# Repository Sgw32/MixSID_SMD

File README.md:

# MixSID - SMD version
*flexible Stereo-SID-board with integrated channel mixer*

The MixSID is a stereo SID board for the C64 that can be used with any combination 
of SID models on a wide range of C64 mainboards.

Features include an integrated stereo channel mixer, 
pragmatic stereo addressing scheme, flexible handling of io areas,
onboard audio input, output and digiboost circuits, 
dedicated stereo output, full paddle compatibility and versatile digital control.

For more information, please see the project page, available in both 
[english](http://www.henning-bekel.de/mixsid) and [german](http://www.henning-bekel.de/mixsid/de).

SMD version is fully compatible with original one from Henning Bekel, also it is licensed and released as a derivative using GPL license. 

GNU GENERAL PUBLIC LICENSE
Version 2, June 1991 (see more on project page)

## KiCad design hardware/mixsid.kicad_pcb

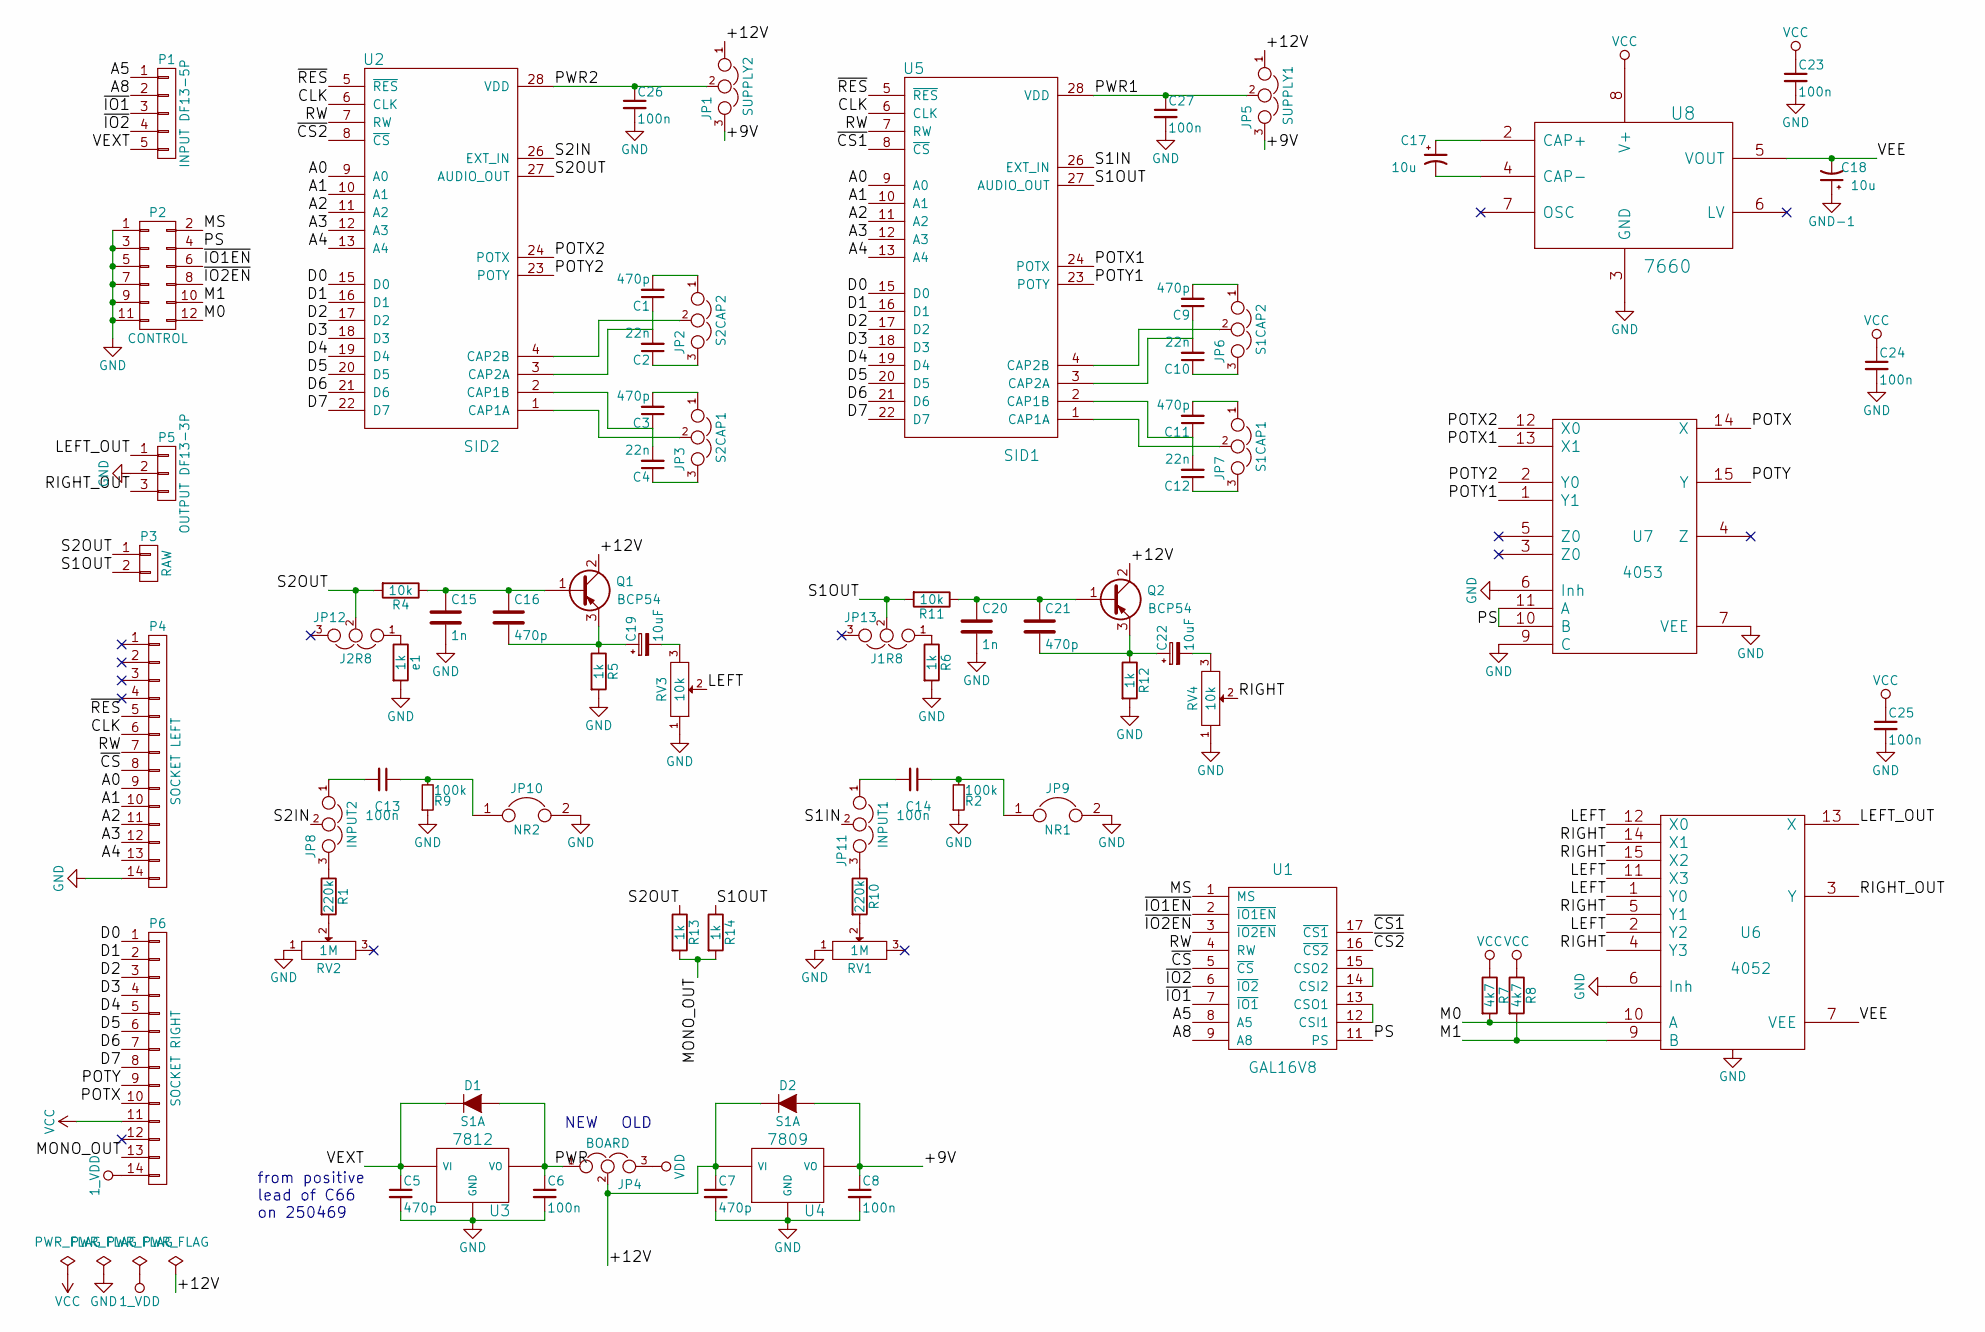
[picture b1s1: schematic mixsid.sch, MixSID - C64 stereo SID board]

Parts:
C1, C3, C5, C7, C9, C11, C16, C21: 470p; 0805
C2, C4, C10, C12: 22n; 0805
C6, C8, C13, C14, C23, C24, C25, C26, C27: 100n; 0805
C15, C20: 1n; 0805
C17, C18: 10u; 0805
C19, C22: 10uF; 0805
D1, D2: S1A; DO-214AC
JP1: SUPPLY2; Pin_Header_Straight_1x03_Pitch2.00mm
JP2: S2CAP2; Pin_Header_Straight_1x03_Pitch2.00mm
JP3: S2CAP1; Pin_Header_Straight_1x03_Pitch2.00mm
JP4: BOARD; Pin_Header_Straight_1x03
JP5: SUPPLY1; Pin_Header_Straight_1x03_Pitch2.00mm
JP6: S1CAP2; Pin_Header_Straight_1x03_Pitch2.00mm
JP7: S1CAP1; Pin_Header_Straight_1x03_Pitch2.00mm
JP8: INPUT2; Pin_Header_Straight_1x03_Pitch2.00mm
JP9: NR1; Pin_Header_Straight_1x02
JP10: NR2; Pin_Header_Straight_1x02
JP11: INPUT1; Pin_Header_Straight_1x03_Pitch2.00mm
JP12: J2R8; Pin_Header_Straight_1x03_Pitch2.00mm
JP13: J1R8; Pin_Header_Straight_1x03_Pitch2.00mm
P1: INPUT DF13-5P; DF13-5P
P2: CONTROL; Pin_Header_Straight_2x06
P3: RAW; Pin_Header_Straight_1x02
P4: SOCKET LEFT; Pin_Header_Straight_1x14
P5: OUTPUT DF13-3P; DF13-3P
P6: SOCKET RIGHT; Pin_Header_Straight_1x14
Q1, Q2: BCP54; SOT-223
R1, R10: 220k; 0805
R2, R9: 100k; 0805
R4, R11: 10k; 0805
R5, R6, R12, R13, R14: 1k; 0805
R7, R8: 4k7; 0805
RV1, RV2: 1M; Potentiometer_Bourns_3296W_3-8Zoll_Inline_ScrewUp
RV3, RV4: 10k; Potentiometer_Bourns_3339P_Angular_ScrewUp
U1: GAL16V8; DIP-20_W7.62mm
U2: SID2; DIP-28_W15.24mm
U3: 7812; TO-252-2
U4: 7809; TO-252-2
U5: SID1; DIP-28_W15.24mm
U6: 4052; SOIC-16
U7: 4053; SOIC-16
U8: 7660; SOIC-8
e1: 1k; 0805

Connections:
/+9V: C8.1, D2.2 (A), JP1.3, JP5.3, U4.3 (VO)
/+12V: C7.1, D2.1 (K), JP1.1, JP4.2, JP5.1, Q1.2 (C), Q2.2 (C), U4.1 (VI)
/A0: P4.9, U2.9 (A0), U5.9 (A0)
/A1: P4.10, U2.10 (A1), U5.10 (A1)
/A2: P4.11, U2.11 (A2), U5.11 (A2)
/A3: P4.12, U2.12 (A3), U5.12 (A3)
/A4: P4.13, U2.13 (A4), U5.13 (A4)
/A5: P1.1, U1.8 (A5)
/A8: P1.2, U1.9 (A8)
/CLK: P4.6, U2.6 (CLK), U5.6 (CLK)
/D0: P6.1, U2.15 (D0), U5.15 (D0)
/D1: P6.2, U2.16 (D1), U5.16 (D1)
/D2: P6.3, U2.17 (D2), U5.17 (D2)
/D3: P6.4, U2.18 (D3), U5.18 (D3)
/D4: P6.5, U2.19 (D4), U5.19 (D4)
/D5: P6.6, U2.20 (D5), U5.20 (D5)
/D6: P6.7, U2.21 (D6), U5.21 (D6)
/D7: P6.8, U2.22 (D7), U5.22 (D7)
/LEFT: RV3.2, U6.1 (Y0), U6.2 (Y2), U6.11 (X3), U6.12 (X0)
/LEFT_OUT: P5.1, U6.13 (X)
/M0: P2.12, R7.2, U6.10 (A)
/M1: P2.10, R8.2, U6.9 (B)
/MONO_OUT: P6.13, R13.2, R14.2
/MS: P2.2, U1.1 (MS)
/POTX: P6.10, U7.14 (X)
/POTX1: U5.24 (POTX), U7.13 (X1)
/POTX2: U2.24 (POTX), U7.12 (X0)
/POTY: P6.9, U7.15 (Y)
/POTY1: U5.23 (POTY), U7.1 (Y1)
/POTY2: U2.23 (POTY), U7.2 (Y0)
/PS: P2.4, U1.11 (PS), U7.10 (B), U7.11 (A)
/PWR: C6.1, D1.2 (A), JP4.1, U3.3 (VO)
/PWR1: C27.1, JP5.2, U5.28 (VDD)
/PWR2: C26.1, JP1.2, U2.28 (VDD)
/RIGHT: RV4.2, U6.4 (Y3), U6.5 (Y1), U6.14 (X1), U6.15 (X2)
/RIGHT_OUT: P5.3, U6.3 (Y)
/RW: P4.7, U1.4 (RW), U2.7 (RW), U5.7 (RW)
/S1IN: JP11.2, U5.26 (EXT_IN)
/S1OUT: JP13.2, P3.2, R11.2, R14.1, U5.27 (AUDIO_OUT)
/S2IN: JP8.2, U2.26 (EXT_IN)
/S2OUT: JP12.2, P3.1, R4.2, R13.1, U2.27 (AUDIO_OUT)
/VEE: C18.2, U6.7 (VEE), U8.5 (VOUT)
/VEXT: C5.1, D1.1 (K), P1.5, U3.1 (VI)
/~CS1: U1.17 (~CS1), U5.8 (~CS)
/~CS2: U1.16 (~CS2), U2.8 (~CS)
/~CS: P4.8, U1.5 (~CS)
/~IO1EN: P2.6, U1.2 (~IO1EN)
/~IO1: P1.3, U1.7 (~IO1)
/~IO2EN: P2.8, U1.3 (~IO2EN)
/~IO2: P1.4, U1.6 (~IO2)
/~RES: P4.5, U2.5 (~RES), U5.5 (~RES)
unnamed: C1.1, C2.2, U2.3 (CAP2A)
unnamed: C1.2, JP2.1
unnamed: C2.1, JP2.3
unnamed: C3.1, C4.2, U2.2 (CAP1B)
unnamed: C3.2, JP3.1
unnamed: C4.1, JP3.3
unnamed: C9.2, JP6.1
unnamed: C10.1, JP6.3
unnamed: C9.1, C10.2, U5.3 (CAP2A)
unnamed: C11.1, C12.2, U5.2 (CAP1B)
unnamed: C11.2, JP7.1
unnamed: C12.1, JP7.3
unnamed: C13.1, JP10.1, R9.2
unnamed: C13.2, JP8.1
unnamed: C14.1, JP9.1, R2.2
unnamed: C14.2, JP11.1
unnamed: C15.1, C16.1, Q1.1 (B), R4.1
unnamed: C16.2, C19.1, Q1.3 (E), R5.1
unnamed: C17.1, U8.2 (CAP+)
unnamed: C17.2, U8.4 (CAP-)
unnamed: C19.2, RV3.3
unnamed: C20.1, C21.1, Q2.1 (B), R11.1
unnamed: C21.2, C22.1, Q2.3 (E), R12.1
unnamed: C22.2, RV4.3
unnamed: JP2.2, U2.4 (CAP2B)
unnamed: JP3.2, U2.1 (CAP1A)
unnamed: JP6.2, U5.4 (CAP2B)
unnamed: JP7.2, U5.1 (CAP1A)
unnamed: JP8.3, R1.1
unnamed: JP11.3, R10.1
unnamed: JP12.1, e1.1
unnamed: JP13.1, R6.1
unnamed: R1.2, RV2.2
unnamed: R10.2, RV1.2
unnamed: U1.12 (CSI1), U1.13 (CSO1)
unnamed: U1.14 (CSI2), U1.15 (CSO2)
VCC: C23.1, C24.1, C25.1, P6.11, R7.1, R8.1, U1.20 (VCC), U2.25 (VCC), U5.25 (VCC), U6.16 (VCC), U7.16 (VCC), U8.8 (V+)

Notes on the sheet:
NEW
OLD
from positive lead of C66 on 250469

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
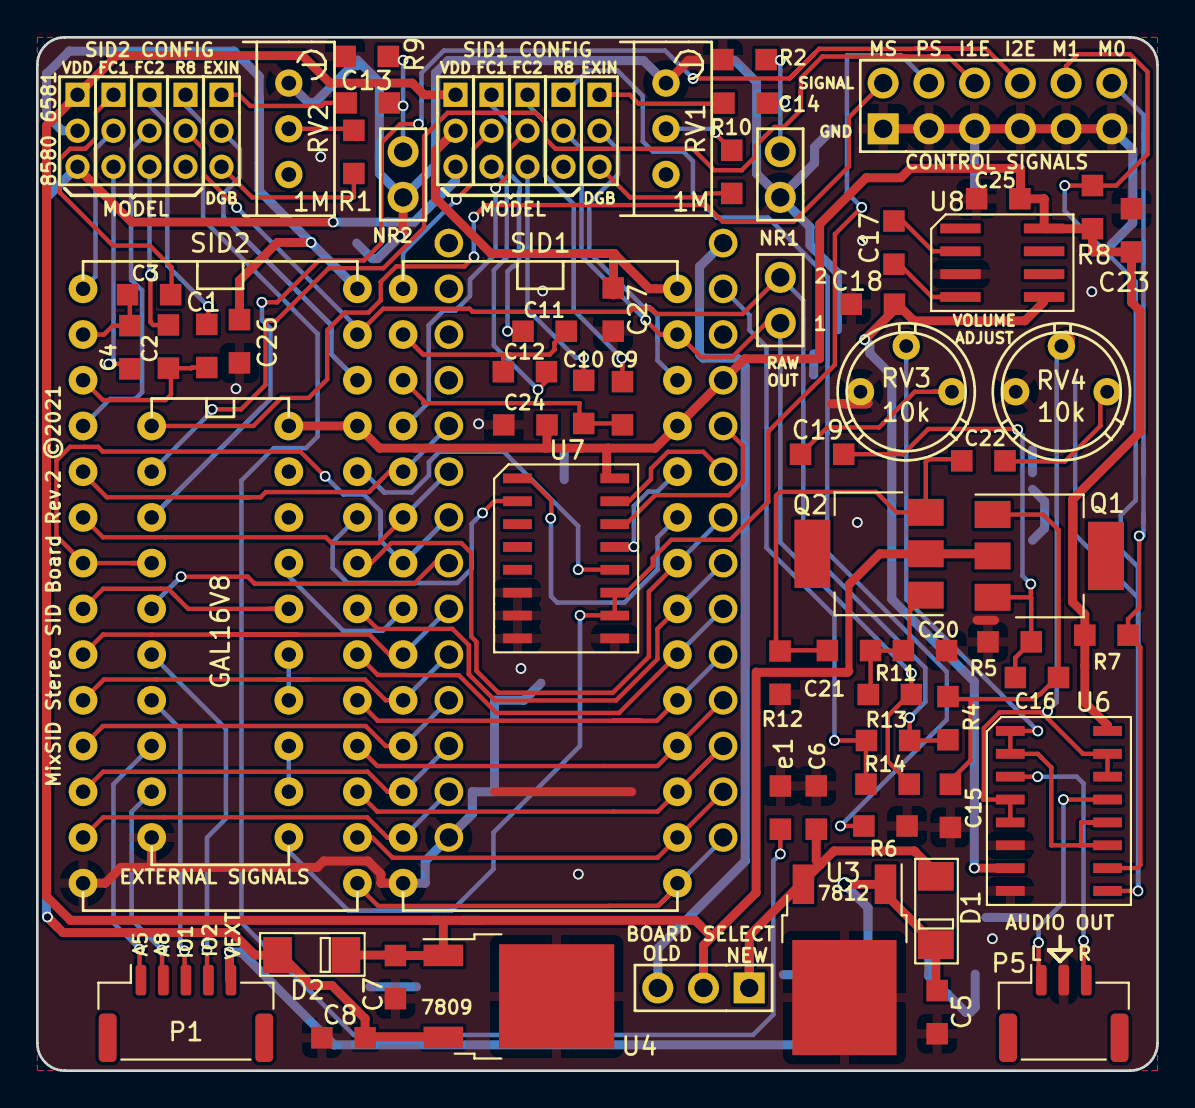
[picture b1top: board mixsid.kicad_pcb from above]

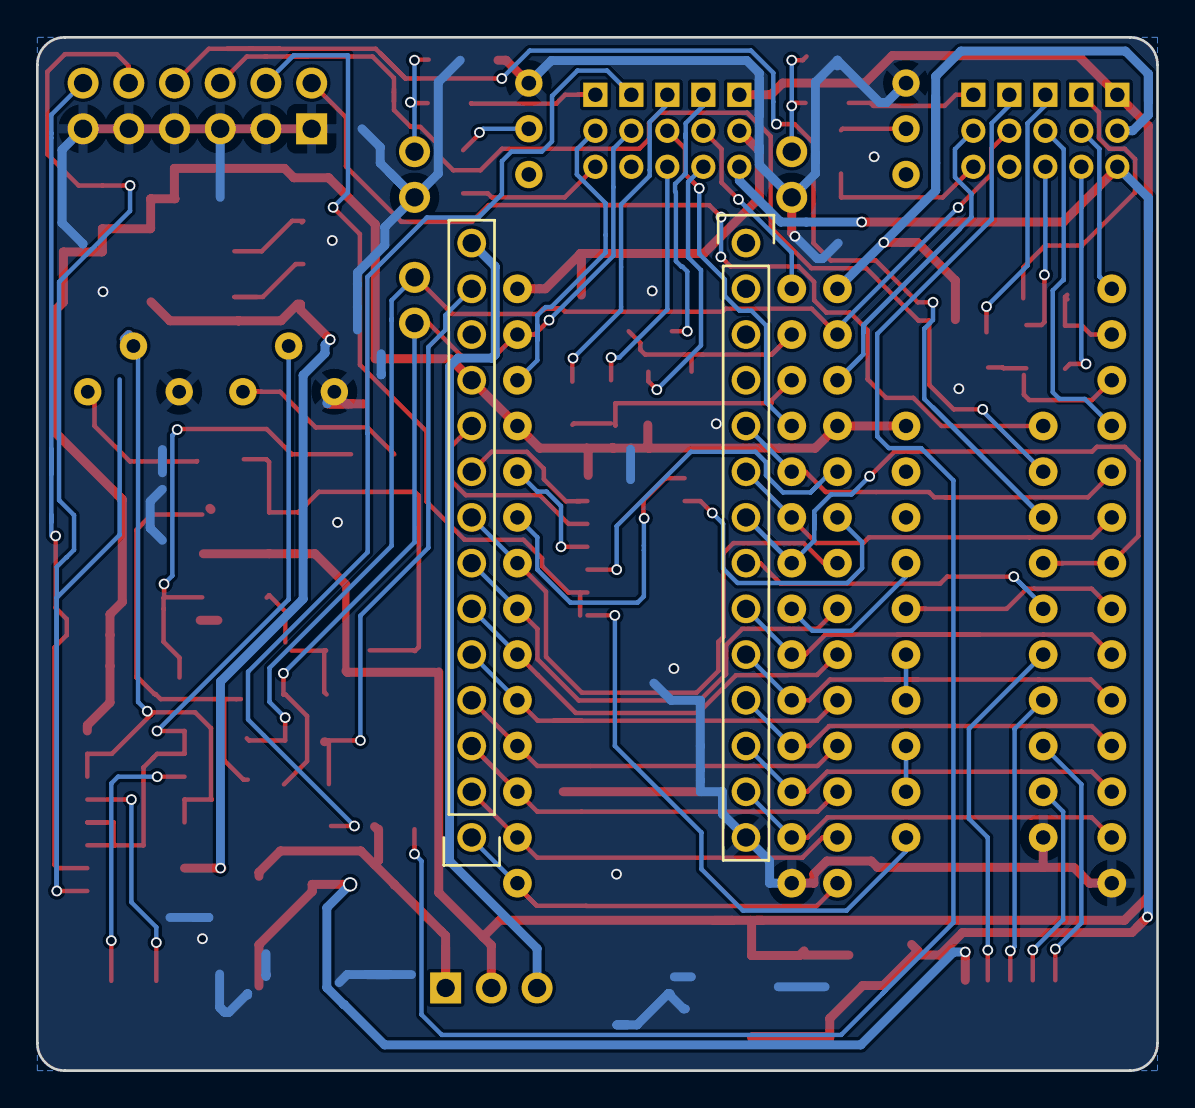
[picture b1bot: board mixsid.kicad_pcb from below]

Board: 2 copper layers, 62.2 x 57.4 mm, 76 parts (2 on the bottom side), 90 nets.

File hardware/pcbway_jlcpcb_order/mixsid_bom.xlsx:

Comment | Designator | Footprint | JLCPCB Part #（optional）
74HC4053 | U7 | SOIC-16
100n | C27,C24,C14,C13,C26,C8,C6,C25,C23 | 0805
220k | R10,R1 | 0805
100k | R2,R9 | 0805
22n | C12,C10,C4,C2 | 0805
470p | C11,C9,C3,C1,C7,C5,C16,C21 | 0805
DF13-3P | P5 | DF13-3P
DF13-3P | P1 | DF13-5P
CJ7809 | U4 | TO-252-2 | C177737
CJ7812 | U3 | TO-252-2 | C26184
S1A | D2,D1 | DO-214AC
10u | C18,C17 | 0805
1k | R6,R14,R13,e1,R12,R5 | 0805
10k | R11,R4 | 0805
1n | C15,C20 | 0805
BCP54 | Q2,Q1 | SOT-223
74hc4052 | U6 | SOIC-16
10uF | C22,C19 | 0805
4k7 | R8,R7 | 0805
XL7660 | U8 | SOIC-8

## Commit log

2023-01-02 MixSID_SMD
2023-01-02 Order files
2025-02-20 Adjust connectors to match JST GH

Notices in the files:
hardware/mixsid.kicad_pcb:
MixSID Stereo SID Board Rev.2 ©2021
